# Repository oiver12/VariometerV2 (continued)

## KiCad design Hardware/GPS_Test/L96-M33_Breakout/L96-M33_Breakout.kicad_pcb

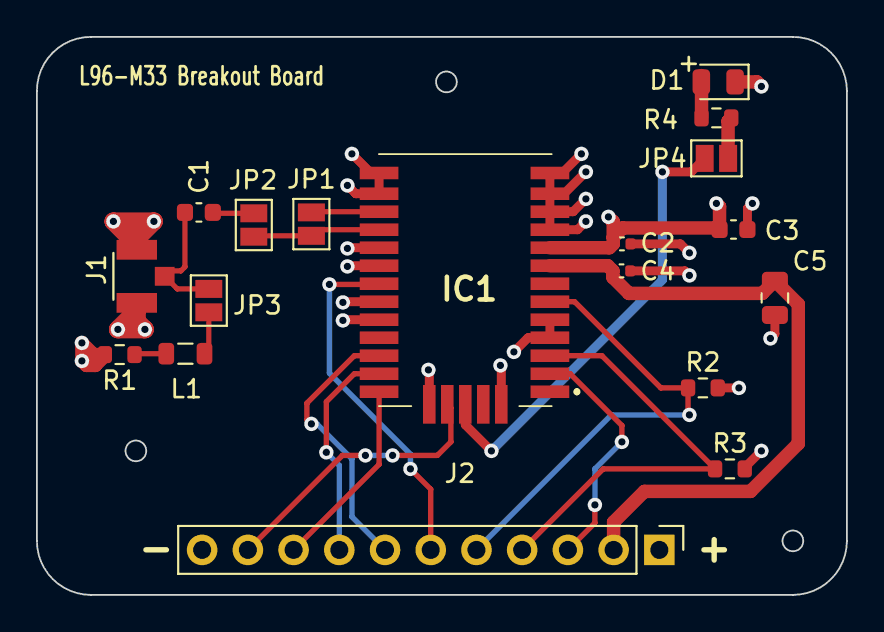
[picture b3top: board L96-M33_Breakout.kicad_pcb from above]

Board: 4 copper layers, 45.0 x 31.0 mm, 18 parts (0 on the bottom side), 20 nets.

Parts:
C1: 100pF; C_0603_1608Metric
C2, C4: 100nF; C_0402_1005Metric
C3: 10uF; C_0603_1608Metric
C5: 4.7uF; C_0805_2012Metric
D1: BLUE; LED_0805_2012Metric
IC1: L96-M33; L96
J1: U.FL-R-SMT(01); HRS_U.FL-R-SMT(01)
J2: Conn_01x11; PinHeader_1x11_P2.54mm_Vertical
JP1, JP2, JP3: SJ; SolderJumper-2_P1.3mm_Open_Pad1.0x1.5mm
JP4: JMP; SolderJumper-2_P1.3mm_Open_Pad1.0x1.5mm
L1: 47nH; L_0805_2012Metric
R1: 10R; R_0603_1608Metric
R2, R3: 4.7k; R_0603_1608Metric
R4: 1k; R_0603_1608Metric

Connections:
3D_FIX: IC1.2 (3D_FIX), J2.3
+3.3V: C2.2, C3.2, IC1.9 (VDD), J2.1, R1.2, R2.2, R3.2
+BATT: C4.2, C5.2, IC1.8 (V_BCKP), J2.2
FORCE_ON: IC1.28 (FORCE_ON), J2.10
GEO_FENCE: IC1.24 (GEO_FENCE), J2.7
GND: C2.1, C3.1, C4.1, C5.1, D1.1 (K), IC1.4 (GND1), IC1.5 (GND2), IC1.10 (GND3), IC1.11 (GND4), IC1.12 (GND5), IC1.13 (GND6), IC1.14 (GND7), IC1.15 (GND8), IC1.18 (GND9), IC1.19 (GND10), IC1.21 (GND11), IC1.22 (GND12), IC1.27 (GND13), IC1.31 (GND14), J1.1 (GND), J1.2 (GND), J2.11
JAM_DET: IC1.20 (JAM_DET), J2.6
unnamed: D1.2 (A), R4.2
unnamed: C1.1, J1.3 (SIG), JP3.1 (A)
unnamed: C1.2, JP2.2 (B)
unnamed: JP3.2 (B), L1.1
unnamed: JP4.1 (A), R4.1
unnamed: L1.2, R1.1
PPS: IC1.29 (TIMEPULSE), JP4.2 (B)
RF_IN: IC1.17 (RF_IN), JP1.2 (B), JP2.1 (A)
RF_OUT: IC1.16 (RF_OUT), JP1.1 (A)
RX: IC1.26 (RXD1), J2.9
SCL: IC1.6 (I2C_SCL), J2.5, R2.1
SDA: IC1.3 (I2C_SDA), J2.4, R3.1
TX: IC1.25 (TXD1), J2.8

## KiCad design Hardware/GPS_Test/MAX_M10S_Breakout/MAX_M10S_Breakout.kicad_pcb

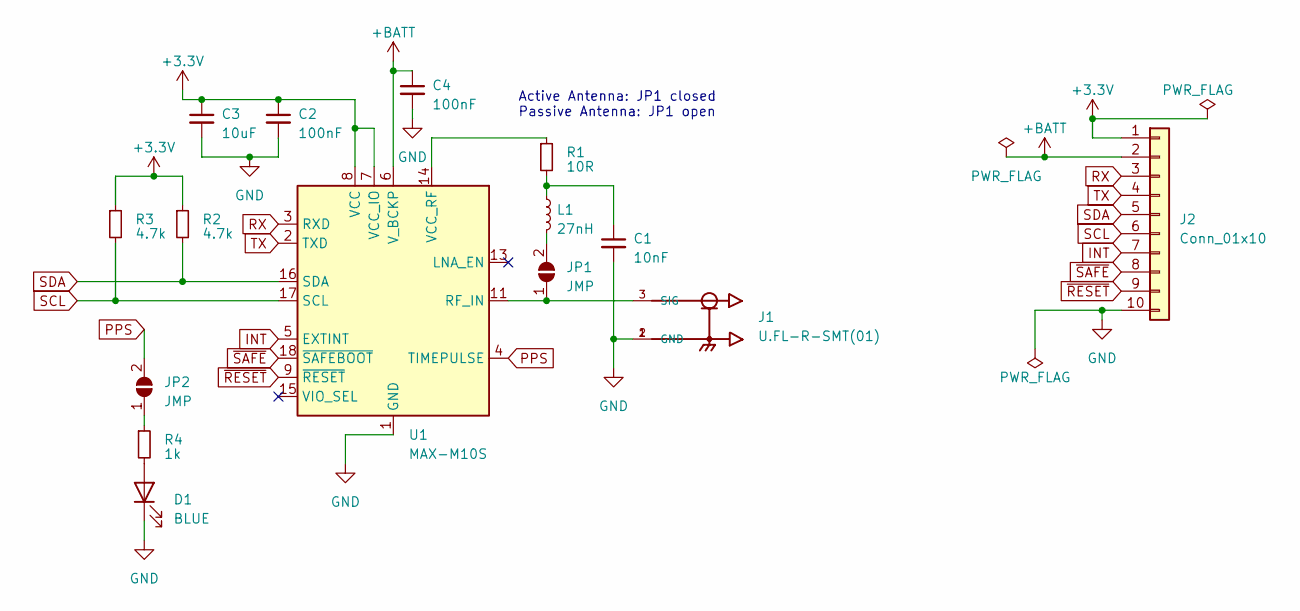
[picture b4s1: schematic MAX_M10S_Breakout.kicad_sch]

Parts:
C1: 10nF; C_0603_1608Metric; LCSC Part C57112
C2, C4: 100nF; C_0402_1005Metric; LCSC Part C307331
C3: 10uF; C_0603_1608Metric; LCSC Part C19702
D1: BLUE; LED_0603_1608Metric; LCSC Part C72041
J1: U.FL-R-SMT(01); HRS_U.FL-R-SMT(01)
J2: Conn_01x10; PinHeader_1x10_P2.54mm_Vertical
JP1, JP2: JMP; SolderJumper-2_P1.3mm_Open_Pad1.0x1.5mm
L1: 27nH; L_0603_1608Metric; LCSC Part C148128
R1: 10R; R_0402_1005Metric; LCSC Part C25077
R2, R3: 4.7k; R_0402_1005Metric; LCSC Part C25900
R4: 1k; R_0603_1608Metric; LCSC Part C21190
U1: MAX-M10S; ublox_MAX

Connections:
+3.3V: C2.1, C3.1, J2.1, R2.1, R3.1, U1.7 (VCC_IO), U1.8 (VCC)
+BATT: C4.1, J2.2, U1.6 (V_BCKP); also elsewhere on the board
GND: C1.2, C2.2, C3.2, C4.2, D1.1 (K), J1.1 (GND), J1.2 (GND), J2.10, U1.1 (GND), U1.10 (GND), U1.12 (GND); also elsewhere on the board
INT: J2.7, U1.5 (EXTINT)
unnamed: C1.1, L1.1, R1.2
unnamed: D1.2 (A), R4.2
unnamed: J1.3 (SIG), JP1.1 (A), U1.11 (RF_IN)
unnamed: JP1.2 (B), L1.2
unnamed: JP2.1 (A), R4.1
unnamed: R1.1, U1.14 (VCC_RF)
PPS: JP2.2 (B), U1.4 (TIMEPULSE)
RX: J2.3, U1.3 (RXD)
SCL: J2.6, R3.2, U1.17 (SCL)
SDA: J2.5, R2.2, U1.16 (SDA)
TX: J2.4, U1.2 (TXD)
~RESET: J2.9, U1.9 (~RESET)
~SAFE: J2.8, U1.18 (~SAFEBOOT)

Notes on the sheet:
Active Antenna: JP1 closed Passive Antenna: JP1 open

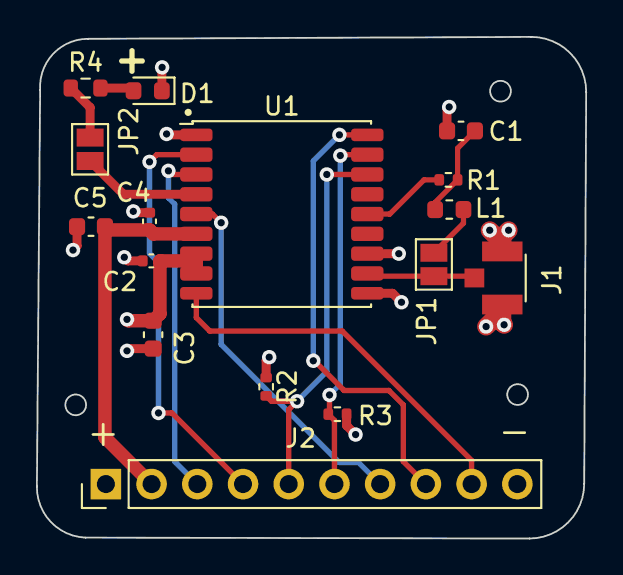
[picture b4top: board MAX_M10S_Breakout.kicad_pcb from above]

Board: 4 copper layers, 30.5 x 27.9 mm, 16 parts (0 on the bottom side), 17 nets.

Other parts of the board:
C5: 4.7uF; C_0603_1608Metric

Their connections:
+BATT: C5.1; also elsewhere on the board
GND: C5.2; also elsewhere on the board

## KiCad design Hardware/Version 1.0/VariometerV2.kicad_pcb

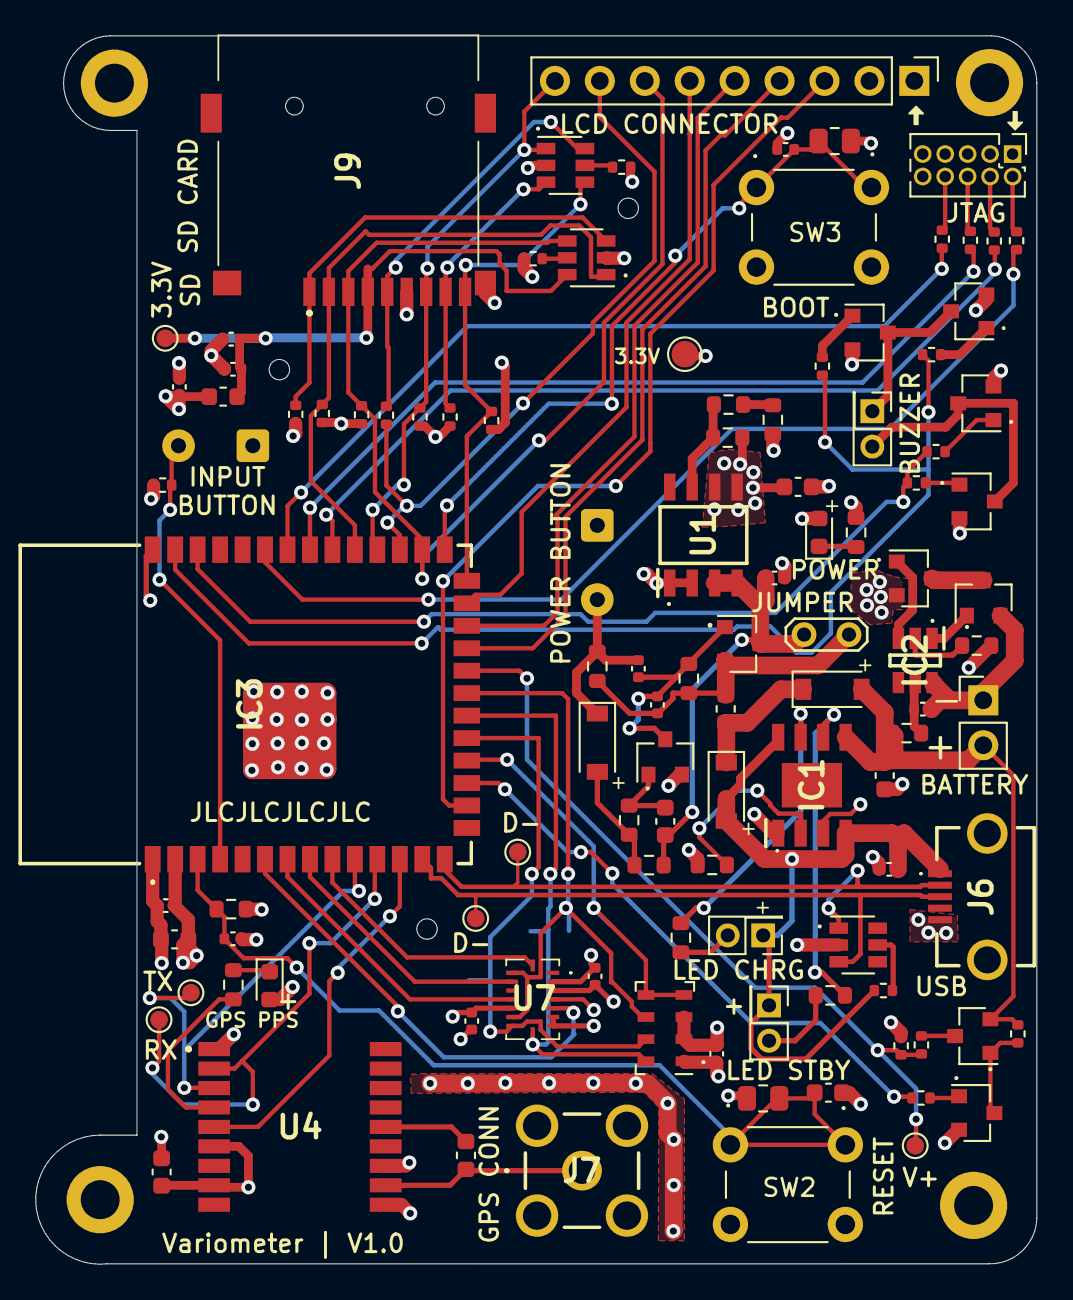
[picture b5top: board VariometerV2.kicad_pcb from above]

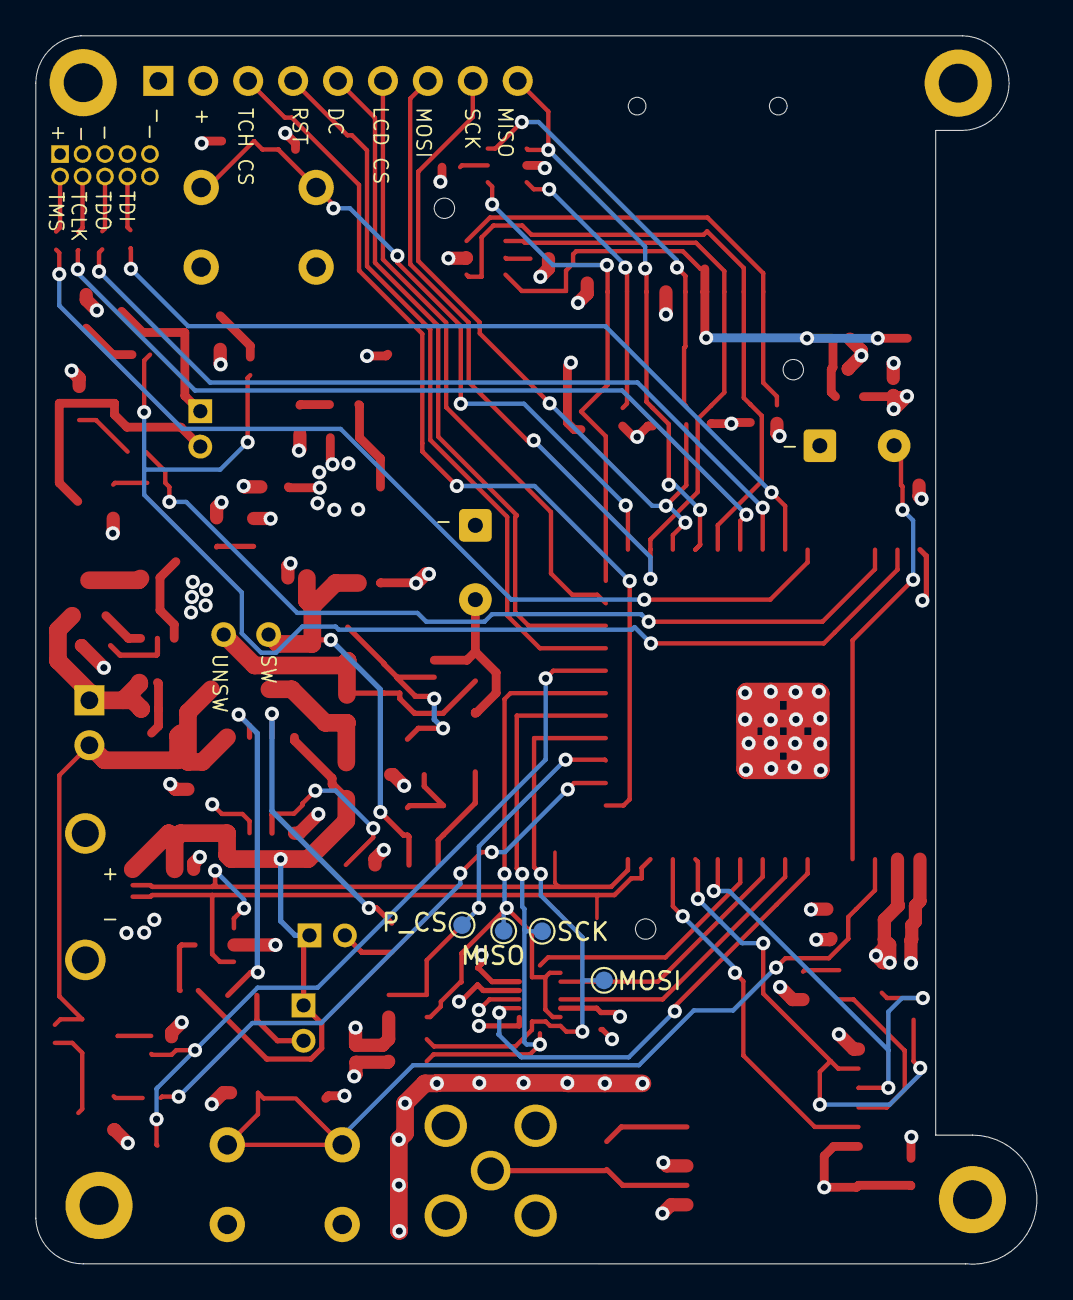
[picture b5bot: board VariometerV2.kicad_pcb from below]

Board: 4 copper layers, 56.6 x 69.4 mm, 117 parts (4 on the bottom side), 82 nets.

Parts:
C1, C2, C5, C7, C10, C13, C18, C19, C20, C21: 100nF; C_0402_1005Metric
C3, C6, C8, C9, C12, C15: 10uF; C_0603_1608Metric
C4, C11: 1uF; C_0402_1005Metric
C16, C17: 2.2uF; C_0402_1005Metric
D1, D2, D3: B5819W SL; D_SOD-123
D4: RED; LED_0603_1608Metric
D5: BLUE; LED_0603_1608Metric
F1: 1A; Fuse_0603_1608Metric
FB1: 600 @ 100 MHz; L_0603_1608Metric
H1, H2, H3, H4: MountingHole_Pad; MountingHole_2.2mm_M2_DIN965_Pad
IC1: TP4056; SOIC127P600X175-9N
IC2: DW01A-G; SOT95P280X135-6N
IC3: ESP32-S3-WROOM-1; ESP32S3WROOM1
J1: LED_CHRG; PinHeader_2x01_P2.00mm_Vertical
J2: LED_STBY; PinHeader_2x01_P2.00mm_Vertical
J3: TFT_LCD_CONNECTOR; PinHeader_1x09_P2.54mm_Vertical
J4: Conn_01x02_Male; PinHeader_1x02_P2.54mm_Vertical
J5: SWD; PinHeader_2x05_P1.27mm_Vertical
J6: USB3135-30-A; USB313530A
J7: 5-1814832-2; 518148322
J8: Conn_02x01; PinHeader_2x01_P2.00mm_Vertical
J9: TFP09-2-12B; TFP09212B
JP1: Jumper_2_Open; TestPoint_2Pads_Pitch2.54mm_Drill0.8mm
L1: 47nH; L_0603_1608Metric
Q1, Q2, Q4, Q6, Q8, Q10: AO3400A; SOT-23
Q3, Q5, Q7, Q9: AO3401A; SOT-23
R1: 1.2k; R_0603_1608Metric
R2, R4, R5, R25: 1k; R_0603_1608Metric
R3: 100; R_0603_1608Metric
R6, R18: 10k; R_0603_1608Metric
R7, R9: 100k; R_0603_1608Metric
R8: 300k; R_0603_1608Metric
R10: 51k; R_0603_1608Metric
R11: 27k; R_0603_1608Metric
R12, R17: 1.5k; R_0603_1608Metric
R13, R38: 1M; R_0402_1005Metric
R14, R16, R24, R26, R27, R28, R29, R30, R31, R32, R33, R34, R36, R37: 10k; R_0402_1005Metric
R15: 33k; R_0402_1005Metric
R19: 4.7k; R_0402_1005Metric
R20, R21, R22, R23, R35: 22; R_0402_1005Metric
R39, R40: 0k; R_0805_2012Metric
SW1, SW4: SW_Push; SolderWire-0.25sqmm_1x02_P4.2mm_D0.65mm_OD1.7mm
SW2, SW3: Switch_SW_Push; SW_PUSH_6mm
TP1: 3.3V TP; TestPoint_Pad_D1.5mm
TP2: TP_3.3V_SD-Card; TestPoint_Pad_D1.0mm
TP3: TP_USB_D+; TestPoint_Pad_D1.0mm
TP4: TP_USB_D-; TestPoint_Pad_D1.0mm
TP5: TP_BATTERY; TestPoint_Pad_D1.0mm
TP6: TP_TX; TestPoint_Pad_D1.0mm
TP7: TP_RX; TestPoint_Pad_D1.0mm
TP8: TP_SPI1_SCK; TestPoint_Pad_D1.0mm
TP9: TP_SPI1_MOSI; TestPoint_Pad_D1.0mm
TP10: TP_SPI1_MISO; TestPoint_Pad_D1.0mm
TP11: TP_PresSens_CS; TestPoint_Pad_D1.0mm
U1: TPS76801QDR; SOIC127P600X175-8N
U2, U5, U6: SRV05-4; SOT-23-6
U4: ATGM336H-5N31; ATGM336H5N31
U7: BMI088
U8: MS5611-01BA; LGA-8_3x5mm_P1.25mm

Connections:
3.3V_SDCARD: C17.1, C18.1, FB1.2, J9.4 (VDD), TP2.1, U5.6 (IO4)
+3V3: C8.1, C9.1, C10.1, C15.1, C16.1, C19.1, C20.1, C21.1, D4.2 (A), D5.2 (A), FB1.1, IC3.2 (3V3), J3.2, J5.1, Q7.2 (S), Q9.2 (S), R10.1, R18.1, R19.1, R30.1, R31.1, R32.1, R33.1, R34.1, R36.1, R37.2, R39.1, R40.1, TP1.1, U1.5 (OUT), U1.6 (OUT), U4.6 (VBAT), U4.8 (VCC), U7.3 (VDD), U7.11 (VDDIO), U8.1 (VDD)
+5V: C1.1, D2.2 (A), IC1.4 (VCC), IC1.8 (CE), J1.1, J2.1, J6.1, R24.1
ACC_INT: IC3.9 (IO16), U7.16 (INT1)
BATT+: C3.1, D1.2 (A), IC1.5 (BAT), J4.2, Q5.2 (S), R3.2, R13.2
BATT_CONN-: C2.1, IC2.6 (GND), J4.1, Q2.2 (S)
BAT_ADC: IC3.22 (IO14), R14.1, R15.2, TP5.1
BAT_MS: IC3.17 (IO9), R16.1
Button_Input: IC3.4 (IO4), R19.2, SW4.2
DW01A_OC: IC2.3 (OC), Q1.1 (G)
DW01A_OD: IC2.1 (OD), Q2.1 (G)
EN: C11.1, C12.1, IC3.3 (EN), R18.2, R39.2, SW2.1
GND: C1.2, C3.2, C7.2, C8.2, C9.2, C10.2, C11.2, C12.2, C13.2, C15.2, C16.2, C17.2, C18.2, C19.2, C20.2, C21.2, H1.1, H2.1, H3.1, H4.1, IC1.1 (Temp), IC1.3 (GND), IC3.1 (GND_1), IC3.40 (GND_2), IC3.41 (GND_3), IC3.42 (GND_4), IC3.43 (GND_5), IC3.44 (GND_6), IC3.45 (GND_7), IC3.46 (GND_8), IC3.47 (GND_9), IC3.48 (GND_10), IC3.49 (GND_11), J3.1, J5.3, J5.5, J5.9, J6.5, J6.MH1, J6.MH2, J7.2, J7.3 (2), J7.4 (2), J7.5 (2), J9.6 (VSS), J9.10 (GND), Q1.2 (S), Q4.2 (S), Q6.2 (S), Q8.2 (S), Q10.2 (S), R1.1, R2.2, R12.2, R15.1, R17.2, R38.2, SW1.1, SW2.2, SW3.2, SW4.1, U1.1 (GND), U1.2 (EN#), U2.2 (VN), U4.1 (GND), U4.10 (GND), U4.12 (GND), U5.2 (VN), U6.2 (VN), U7.2 (NC), U7.4 (GNDA), U7.6 (GNDIO), U7.7 (PS), U8.2 (PS), U8.3 (GND)
GPS_ON: IC3.12 (IO8), U4.5 (ON/OFF)
GPS_PPS: R25.2, U4.4 (1PPS)
GYR_INT: IC3.7 (IO7), U7.12 (INT3)
IMU_ACC_CS: IC3.8 (IO15), U7.14 (CSB1)
IMU_GYR_CS: IC3.6 (IO6), U7.5 (CSB2)
IO0: C13.1, IC3.27 (IO0), R40.2, SW3.1
JTAG_TCLK: IC3.32 (IO39), R21.2
JTAG_TDI: IC3.34 (IO41), R23.2
JTAG_TDO: IC3.33 (IO40), R22.2
JTAG_TMS: IC3.35 (IO42), R20.2
LCD_CS: IC3.25 (IO48), J3.6
LCD_DC: IC3.24 (IO47), J3.5
LCD_RST: IC3.23 (IO21), J3.4
LCD_TCH_CS: IC3.16 (IO46), J3.3
unnamed: C2.2, IC2.5 (VCC), R3.1
unnamed: C4.1, C5.1, Q3.1 (G), Q4.3 (D), R7.2
unnamed: C4.2, D3.1 (K), R6.2, SW1.2
unnamed: C6.1, Q4.1 (G), R8.2
unnamed: D1.1 (K), D2.1 (K), F1.2
unnamed: D3.2 (A), R8.1, R9.2
unnamed: D4.1 (K), R17.1
unnamed: D5.1 (K), R25.1
unnamed: IC1.2 (PROG), R1.2
unnamed: IC2.2 (CS), R2.1
unnamed: J1.2, R4.1
unnamed: J2.2, R5.1
unnamed: J5.2, R20.1
unnamed: J5.4, R21.1
unnamed: J5.6, R22.1
unnamed: J5.8, R23.1
unnamed: J7.1, L1.1, U4.11 (RF_IN)
unnamed: J8.1, Q7.3 (D), Q8.3 (D)
unnamed: J8.2, Q9.3 (D), Q10.3 (D)
unnamed: J9.1 (DAT2), R30.2, U5.3 (IO2)
unnamed: J9.5 (CLK), R35.2, U6.6 (IO4)
unnamed: J9.8 (DAT1), R34.2, U6.3 (IO2)
unnamed: L1.2, U4.14 (VCC_RF)
unnamed: Q1.3 (D), Q2.3 (D)
unnamed: Q5.1 (G), Q6.3 (D), R13.1
unnamed: Q5.3 (D), R14.2
unnamed: Q6.1 (G), R16.2
unnamed: Q7.1 (G), R26.1
unnamed: Q8.1 (G), R27.1
unnamed: Q9.1 (G), R28.2
unnamed: Q10.1 (G), R29.2
unnamed: R10.2, R11.1, U1.7 (FB/NC)
unnamed: R11.2, R12.1
unnamed: R24.2, U2.5 (VP)
unnamed: R36.2, U5.5 (VP)
unnamed: R37.1, U6.5 (VP)
POW_SW+: C6.2, C7.1, JP1.2 (B), Q3.3 (D), R9.1, U1.3 (IN), U1.4 (IN)
POW_UNSW+: C5.2, F1.1, JP1.1 (A), Q3.2 (S), R6.1, R7.1
PresSens_CS: IC3.18 (IO10), TP11.1, U8.4 (CSB), U8.5 (CSB)
SDCARD_CS: IC3.31 (IO38), J9.2 (CD/DAT3), R31.2, U5.1 (IO1)
SDCARD_DETECT: IC3.26 (IO45), J9.9 (CARD_DETECTION), R38.1, U6.4 (IO3)
SPI1_MISO: IC3.21 (IO13), TP10.1, U7.10 (SDO2), U7.15 (SDO1), U8.6 (SDO)
SPI1_MOSI: IC3.19 (IO11), TP9.1, U7.9 (SDI), U8.7 (SDI/SDA)
SPI1_SCK: IC3.20 (IO12), TP8.1, U7.8 (SCK), U8.8 (SCLK)
SPI2_MISO: IC3.30 (IO37), J3.9, J9.7 (DAT0), R33.2, U6.1 (IO1)
SPI2_MOSI: IC3.28 (IO35), J3.7, J9.3 (CMD), R32.2, U5.4 (IO3)
SPI2_SCK: IC3.29 (IO36), J3.8, R35.1
TIM1_CH1: IC3.39 (IO1), R26.2, R27.2
TIM1_CH1N: IC3.38 (IO2), R28.1, R29.1
TP4056_CHRG: IC1.7 (CHRG), R4.2
TP4056_STBY: IC1.6 (STDBY), R5.2
USART2_RX: IC3.11 (IO18), TP7.1, U4.2 (TXD)
USART2_TX: IC3.10 (IO17), TP6.1, U4.3 (RXD)
USB_D+: IC3.14 (IO20), J6.2, TP3.1, U2.1 (IO1)
USB_D-: IC3.13 (IO19), J6.3, TP4.1, U2.3 (IO2)

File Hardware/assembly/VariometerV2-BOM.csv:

Comment,Designator,Footprint,LCSC
"100nF","C1,C2,C5,C7,C10,C13,C18,C19,C20,C21","Capacitor_SMD:C_0402_1005Metric","C307331"
"2.2uF","C16,C17","Capacitor_SMD:C_0402_1005Metric","C12530"
"10uF","C3,C6,C8,C9,C12,C15","Capacitor_SMD:C_0603_1608Metric","C19702"
"1uF","C4,C11","Capacitor_SMD:C_0402_1005Metric","C52923"
"B5819W SL","D1,D2,D3","Diode_SMD:D_SOD-123","C8598"
"RED","D4","LED_SMD:LED_0603_1608Metric","C2286"
"BLUE","D5","LED_SMD:LED_0603_1608Metric","C72041"
"1A","F1","Fuse:Fuse_0603_1608Metric","C516069"
"600 @ 100 MHz","FB1","Inductor_SMD:L_0603_1608Metric","C1002"
"MountingHole_Pad","H1,H2,H3,H4","MountingHole:MountingHole_2.2mm_M2_DIN965_Pad",""
"TP4056","IC1","Hardware:SOIC127P600X175-9N","C16581"
"DW01A-G","IC2","Hardware:SOT95P280X135-6N","C61503"
"ESP32-S3-WROOM-1","IC3","Hardware:ESP32S3WROOM1","C2913198"
"LED_CHRG","J1","Connector_PinHeader_2.00mm:PinHeader_2x01_P2.00mm_Vertical",""
"LED_STBY","J2","Connector_PinHeader_2.00mm:PinHeader_2x01_P2.00mm_Vertical",""
"TFT_LCD_CONNECTOR","J3","Connector_PinHeader_2.54mm:PinHeader_1x09_P2.54mm_Vertical",""
"Conn_01x02_Male","J4","Connector_PinHeader_2.54mm:PinHeader_1x02_P2.54mm_Vertical",""
"SWD","J5","Connector_PinHeader_1.27mm:PinHeader_2x05_P1.27mm_Vertical",""
"USB3135-30-A","J6","Hardware:USB313530A",""
"5-1814832-2","J7","Hardware:518148322",""
"Conn_02x01","J8","Connector_PinHeader_2.00mm:PinHeader_2x01_P2.00mm_Vertical",""
"TFP09-2-12B","J9","Hardware:TFP09212B",""
"Jumper_2_Open","JP1","TestPoint:TestPoint_2Pads_Pitch2.54mm_Drill0.8mm",""
"47nH","L1","Inductor_SMD:L_0603_1608Metric","C346317"
"AO3400A","Q1,Q2,Q4,Q6,Q8,Q10","Package_TO_SOT_SMD:SOT-23","C20917"
"AO3401A","Q3,Q5,Q7,Q9","Package_TO_SOT_SMD:SOT-23","C15127"
"1.2k","R1","Resistor_SMD:R_0603_1608Metric","C22765"
"51k","R10","Resistor_SMD:R_0603_1608Metric","C23196"
"27k","R11","Resistor_SMD:R_0603_1608Metric","C22967"
"1.5k","R12,R17","Resistor_SMD:R_0603_1608Metric","C22843"
"1M","R13,R38","Resistor_SMD:R_0402_1005Metric","C26083"
"10k","R14,R16,R24,R26,R27,R28,R29,R30,R31,R32,R33,R34,R36,R37","Resistor_SMD:R_0402_1005Metric","C25744"
"33k","R15","Resistor_SMD:R_0402_1005Metric","C25779"
"4.7k","R19","Resistor_SMD:R_0402_1005Metric","C25900"
"1k","R2,R4,R5,R25","Resistor_SMD:R_0603_1608Metric","C21190"
"22","R20,R21,R22,R23,R35","Resistor_SMD:R_0402_1005Metric","C25092"
"100","R3","Resistor_SMD:R_0603_1608Metric","C22775"
"0k","R39,R40","Resistor_SMD:R_0805_2012Metric",""
"10k","R6,R18","Resistor_SMD:R_0603_1608Metric","C25804"
"100k","R7,R9","Resistor_SMD:R_0603_1608Metric","C25803"
"300k","R8","Resistor_SMD:R_0603_1608Metric","C23024"
"SW_Push","SW1,SW4","Connector_Wire:SolderWire-0.25sqmm_1x02_P4.2mm_D0.65mm_OD1.7mm",""
"Switch_SW_Push","SW2,SW3","Button_Switch_THT:SW_PUSH_6mm",""
"3.3V TP","TP1","TestPoint:TestPoint_Pad_D1.5mm",""
"TP_SPI1_MISO","TP10","TestPoint:TestPoint_Pad_D1.0mm",""
"TP_PresSens_CS","TP11","TestPoint:TestPoint_Pad_D1.0mm",""
"TP_3.3V_SD-Card","TP2","TestPoint:TestPoint_Pad_D1.0mm",""
"TP_USB_D+","TP3","TestPoint:TestPoint_Pad_D1.0mm",""
"TP_USB_D-","TP4","TestPoint:TestPoint_Pad_D1.0mm",""
"TP_BATTERY","TP5","TestPoint:TestPoint_Pad_D1.0mm",""
"TP_TX","TP6","TestPoint:TestPoint_Pad_D1.0mm",""
"TP_RX","TP7","TestPoint:TestPoint_Pad_D1.0mm",""
"TP_SPI1_SCK","TP8","TestPoint:TestPoint_Pad_D1.0mm",""
"TP_SPI1_MOSI","TP9","TestPoint:TestPoint_Pad_D1.0mm",""
"TPS76801QDR","U1","Hardware:SOIC127P600X175-8N","C20030"
"SRV05-4","U2,U5,U6","Package_TO_SOT_SMD:SOT-23-6","C85364"
"ATGM336H-5N31","U4","Hardware:ATGM336H5N31","C90770"
"BMI088","U7","Hardware:BMI088","C194919"
"MS5611-01BA","U8","Package_LGA:LGA-8_3x5mm_P1.25mm","C37148"

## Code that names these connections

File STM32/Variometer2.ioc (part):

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Mcu.Name=STM32F745V(E-G)Tx
Mcu.Package=LQFP100
Mcu.UserName=STM32F745VETx
PA1.GPIOParameters=GPIO_Label
PA1.GPIO_Label=GPS_PPS
PA1.Signal=GPIO_Input
PA10.Mode=Asynchronous
PA10.Signal=USART1_RX
PA11.Mode=Device_Only
PA11.Signal=USB_OTG_FS_DM
PA12.Mode=Device_Only
PA12.Signal=USB_OTG_FS_DP
PA13.Mode=Trace_Asynchronous_SW
PA13.Signal=SYS_JTMS-SWDIO
PA14.Mode=Trace_Asynchronous_SW
PA14.Signal=SYS_JTCK-SWCLK
PA2.Mode=Asynchronous
PA2.Signal=USART2_TX
PA3.Mode=Asynchronous
PA3.Signal=USART2_RX
PA4.GPIOParameters=GPIO_Label
PA4.GPIO_Label=GPS_ON/OFF
PA4.Signal=GPIO_Output
PA5.Mode=Full_Duplex_Master
PA5.Signal=SPI1_SCK
PA6.Mode=Full_Duplex_Master
PA6.Signal=SPI1_MISO
PA7.Mode=Full_Duplex_Master
PA7.Signal=SPI1_MOSI
PA9.Mode=Asynchronous
PA9.Signal=USART1_TX
PB0.GPIOParameters=GPIO_Label
PB0.GPIO_Label=IMU_GYR_CS
PB0.Signal=GPIO_Output
PB1.GPIOParameters=GPIO_Label
PB1.GPIO_Label=ACC_INT
PB1.Signal=GPXTI1
PB13.GPIOParameters=GPIO_Label
PB13.GPIO_Label=BLE_LED
PB13.Signal=GPIO_Output
PB14.GPIOParameters=GPIO_Label
PB14.GPIO_Label=GPS_LED
PB14.Signal=GPIO_Output
PB15.GPIOParameters=GPIO_Label
PB15.GPIO_Label=ERROR_LED
PB15.Signal=GPIO_Output
PB2.GPIOParameters=GPIO_Label
PB2.GPIO_Label=GYR_INT
PB2.Signal=GPXTI2
PB3.Mode=Trace_Asynchronous_SW
PB3.Signal=SYS_JTDO-SWO
PC0.GPIOParameters=GPIO_Label
PC0.GPIO_Label=BAT_ADC
PC0.Signal=ADCx_IN10
PC10.Mode=SD_4_bits_Wide_bus
PC10.Signal=SDMMC1_D2
PC11.Mode=SD_4_bits_Wide_bus
PC11.Signal=SDMMC1_D3
PC12.Mode=SD_4_bits_Wide_bus
PC12.Signal=SDMMC1_CK
PC14/OSC32_IN.GPIOParameters=GPIO_Label
PC14/OSC32_IN.GPIO_Label=BAT_MS
PC14/OSC32_IN.Signal=GPIO_Output
PC5.GPIOParameters=GPIO_Label
PC5.GPIO_Label=IMU_ACC_CS
PC5.Signal=GPIO_Output
PC6.GPIOParameters=GPIO_Label
PC6.GPIO_Label=BLE_DATA
PC6.Signal=GPIO_Input
PC7.GPIOParameters=GPIO_Label
PC7.GPIO_Label=BLE_nRESET
PC7.Signal=GPIO_Output
PC8.Mode=SD_4_bits_Wide_bus
PC8.Signal=SDMMC1_D0
PC9.Mode=SD_4_bits_Wide_bus
PC9.Signal=SDMMC1_D1
PD11.GPIOParameters=GPIO_Label
PD11.GPIO_Label=BLE_LINK
PD11.Signal=GPIO_Input
PD12.Mode=I2C
PD12.Signal=I2C4_SCL
PD13.Mode=I2C
PD13.Signal=I2C4_SDA
PD14.GPIOParameters=GPIO_Label
PD14.GPIO_Label=BLE_SLEEP
PD14.Signal=GPIO_Output
PD15.GPIOParameters=GPIO_Label
PD15.GPIO_Label=BLE_MODE
PD15.Signal=GPIO_Output
PD2.Mode=SD_4_bits_Wide_bus
PD2.Signal=SDMMC1_CMD
PD4.GPIOParameters=GPIO_Label
PD4.GPIO_Label=SDCARD_DETECT
PD4.Signal=GPIO_Input
PE0.GPIOParameters=GPIO_PuPd,GPIO_Label
PE0.GPIO_Label=Button_Input
PE0.GPIO_PuPd=GPIO_PULLDOWN
PE0.Signal=GPIO_Input
PE15.GPIOParameters=GPIO_Label
PE15.GPIO_Label=PresSen_CS
PE15.Signal=GPIO_Output
PE8.Mode=Output Compare1 CH1 CH1N
PE8.Signal=TIM1_CH1N
PE9.Signal=S_TIM1_CH1
PH0/OSC_IN.Mode=HSE-External-Oscillator
PH0/OSC_IN.Signal=RCC_OSC_IN
PH1/OSC_OUT.Mode=HSE-External-Oscillator
PH1/OSC_OUT.Signal=RCC_OSC_OUT
RCC.HSE_VALUE=16000000
board=custom

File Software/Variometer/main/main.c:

#include <stdio.h>
#include <esp_log.h>
#include <driver/gpio.h>
#include "nmea_parser.h"
#include "SDCard.h"
#include "main.h"
#include "BatteryManager.h"
#include "SoundManager.h"
#include "IGC/IGCLogger.h"
#include "TestTools/FlightLogger.h"
#include "DeviceContext.h"
#include "Screen/Display_Vario.h"
#include "ButtonInput.h"
#include "AGL.h"
#include "Flash/flashMemory.h"
#include "AirspaceParcer/airspaceParcer.h"
#include "MainTasks.h"
#include "Bluetooth/bluetooth.h"
#include "ErrorHandling.h"

#define POWSW_ENABLE 13

#define I2C_MASTER_FREQ_HZ 80000
#define I2C_SDA 37
#define I2C_SCL 36
#define i2c_master_port 0

#define USART2_TX 17
#define USART2_RX 18

/* GPS */
#define TIME_ZONE (+1)   // Schweiz
#define YEAR_BASE (2000) // date in GPS starts from 2000

static const char *TAG = "main";

// void sendAttitude(void *params)
// {
//     float rotation[4];
//     // float roll = 0.0f, pitch = 0.0f, yaw = 0.0f;
//     while (1)
//     {
//         // Quaternion_get_RPY(rotation[0], rotation[1], rotation[2], rotation[3], &roll, &pitch, &tmep);
//         // fwrite(&roll, sizeof(float), 1, stdout);
//         // fwrite(&pitch, sizeof(float), 1, stdout);
//         // fwrite(&yaw, sizeof(float), 1, stdout);
//         fwrite(&rotation, sizeof(float), 4, stdout);
//         char ending = 0xff;
//         fwrite(&ending, sizeof(char), 1, stdout);
//         printf("\n");
//         vTaskDelay(200 / portTICK_PERIOD_MS);
//     }
//     vTaskDelete(NULL);
// }

void app_main(void)
{
    esp_err_t err;
    gpio_config_t enableGPIOOutput = {
        .intr_type = GPIO_INTR_DISABLE,
        .mode = GPIO_MODE_OUTPUT,
        .pin_bit_mask = 1ULL << POWSW_ENABLE,
        .pull_down_en = 0,
        .pull_up_en = 0};

    err = gpio_config(&enableGPIOOutput);
    err |= gpio_set_level(POWSW_ENABLE, 1);
    if (err != ESP_OK)
    {
        error_handle(err, ERR_MAIN, "Can't initialize Power EN GPIO");
        return;
    }

    vTaskDelay(1000 / portTICK_PERIOD_MS);

    err = gpio_install_isr_service(ESP_INTR_FLAG_LEVEL1); // gpio interrupts are generally not that important
    if (err != ESP_OK)
    {
        error_handle(err, ERR_MAIN, "Can't initialize ISR Service");
    }

    // // /* Configure GPS Reader Library */
    nmea_parser_config_t gps_config = NMEA_PARSER_CONFIG_DEFAULT();
    gps_config.uart.rx_pin = USART2_RX;
    nmea_parser_handle_t gps_nmea_hdl = nmea_parser_init(&gps_config, 5 * 1024);
    ESP_LOGI(TAG, "GPS started");

    // sdcard_t *sdcard = calloc(sizeof(sdcard_t), 1);
    init_DeviceContext();

    err = init_sdcard("/sdcard");
    if (err == ESP_FAIL)
    {
        error_handle(err, ERR_SDCARD, "Can't mount File System");
    }
    else if (err != ESP_OK)
    {
        error_handle(err, ERR_SDCARD, "Can't initialite SD Card");
    }
    init_IGCLogger(gps_nmea_hdl);
    initLogging(gps_nmea_hdl);

    // gps handle wird beim DeviceContext erst nach SD Karte gestartet, da wenn direkt abfulg ist, soll
    // das loggen auf SDKarte direkt starten. Wenn die Sd Karte gestartet wird, muss jedoch device kontext
    // schon gestartet sein
    startGps_DeviceContext(gps_nmea_hdl);

    err = init_SoundManager();
    ERROR_HANDLEBYERROR(err, ERR_SOUNDMANAGER, "Can't start Sound Manager");

    err = init_Display();
    ERROR_HANDLEBYERROR(err, ERR_SCREEN, "Can't start display");

    err = flashMemoryInit();
    ERROR_HANDLEBYERROR(err, ERR_FLASH, "Can't start Flash");

    err = init_Battery_Manager(4);
    ERROR_HANDLEBYERROR(err, ERR_BATTERY, "Can't start Battery Manager");

    err = ButtonInput_Init();
    ERROR_HANDLEBYERROR(err, ERR_BUTTONS, "Can't start Button Manager");

    err = startLogging();
    ERROR_HANDLEBYERROR(err, ERR_LOGGING, "Can't start Testlogging");
    // AGL_startAGL(sdcard, gps_nmea_hdl);

    StartAirspaceParse();

    startBluetooth();

    vTaskDelay(100 / portTICK_PERIOD_MS);

    startMainTasks();
    // xTaskCreate(sendAttitude, "Send Attitude", 4 * 1024, NULL, 6, NULL);
    // perfmon_start();
    return;
}

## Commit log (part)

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2021-11-03 Add Hardware
2021-11-20 Fast fertig
2021-11-29 Fertig
2021-12-06 Schematic Finish
2021-12-31 PCB fast fertig
2022-01-03 PCB fertig
2022-01-13 gerber added
2022-01-14 readme
2022-01-18 esp32 start
2022-01-21 change
2022-01-28 create
2022-03-05 Variometer bestellt
2022-03-06 VSCode started
2022-03-11 Added Kalman Filter
2022-03-17 use I2C
2022-04-09 Change I2C
2022-07-29 Kalman Filter funktioniert
2022-08-27 V2.0 fertig
2022-09-05 Before Variometer V2.2
2022-09-10 Logging Functions
2022-09-20 ScreenTest_Start
2022-10-14 test
2022-10-16 screen
2022-10-17 flgithLogger
2022-11-11 case
2022-11-14 case follow
2022-11-21 case new
2022-12-14 EInk fast working
2022-12-15 E_Ink fast funktioniert
2022-12-16 Screen fast working
2022-12-25 Display fast working
2022-12-30 Bildschirm und Simulator
    -Bildschirm funktioniert
    -Vario Bildschirm Simulator erstellt
    -Bilder können als Buffer ausgegeben werden.
    -Paint Buffer können auf Bildschirm dargestellt werden
2022-12-30 Screen Simulator
2023-01-03 settings start implement
2023-01-14 v1.2 continue
2023-01-14 case_icons
2023-02-01 Buttons working / Case V. 1.3
2023-02-11 Settings fast
2023-02-25 start Airspace
2023-03-09 compass / attitude
2023-03-14 not everything works
2023-03-29 sdcard fix
2023-04-03 Test12
2023-04-05 Linux added
2023-04-10 Start GPS -Test-PCB
2023-04-10 MAX-M10S continue
2023-04-11 Weiter Max M10S
2023-04-11 Folder with cases from saemi. Many blender files, Oli will be pissed.
2023-04-13 Continue GPS Hardware
2023-04-14 Max-M10S finished
2023-04-14 added some boolean outlets
2023-04-17 case version 1.2.0 finished
2023-04-17 Change to esp-idf 5.1
2023-04-17 Fertig GPS Test Platine
2023-04-17 Threejs implementation start
2023-04-18 Rename Readme.me to Readme.md
2023-04-18 Rename Readme.md to README.md
2023-04-18 Fix Screen / Clenaup
2023-04-20 Start Board Devlopment
2023-04-21 Start Vario PCB
2023-04-24 Develop Board
2023-04-27 Working on PCB
2023-04-27 added spinning wheel
2023-04-27 spinning wheel modified
2023-04-27 dependency conflict fixed
2023-04-27 Weiter PCB
2023-04-28 Work on Linux Screen Simulator
2023-05-01 Info text and other smaller details added
2023-05-01 Update Schematics
2023-05-01 Screen Simulator with Height
2023-05-01 Product new pop up changed
2023-05-02 Work on PCB
2023-05-02 Update gitignores
2023-05-02 Change gitignore
2023-05-02 fucked up merge fixed
2023-05-02 pop up finished and info arrow started
2023-05-03 PCB/Screen_Simulator
2023-05-03 fuck me
2023-05-03 Add GPS Info Widget
2023-05-04 before dark theme remove
2023-05-04 second page added
2023-05-04 Add IGC Parser
2023-05-05 IGCParser
2023-05-06 Home page 'finished'
2023-05-07 IGC File Parser
2023-05-08 another try :(
2023-05-10 Add Flight End Screen
2023-05-11 Flight List
2023-05-12 Flig Stat
2023-05-14 three js integration2
2023-05-15 Changfe
2023-05-15 GPS Analyze
2023-05-17 Work on Airspace Parcer
2023-05-17 first and second page added at home for selling website
2023-05-19 sdaf
2023-05-19 Fix Vario Bugs
2023-05-19 New Changes
2023-05-21 GPS Test
2023-05-23 Airspaces
2023-05-23 Airspace Parcer
2023-05-23 AirspaceParcer
2023-05-23 Airspace parsing works on Variometer
2023-05-24 Optimize Airspace Parcer
2023-05-25 Airspace Fixes
2023-05-25 Fixes in Airspace
2023-05-26 GPS Test Files
2023-05-26 Caching IGC Parse
2023-05-30 Fix some Errors
2023-06-01 case version 2.9.0 finished
2023-06-01 Start on pcb
2023-06-02 svg added
2023-06-02 PCb Layout done
2023-06-02 Fix some Errors and Biep Mean
2023-06-05 PCb Work...
2023-06-05 WRL File
2023-06-06 Add Bluetooth BLE
2023-06-06 Bluetooth Works
2023-06-07 Routing ..
2023-06-08 PCB Routing Done
2023-06-08 New 3D File
2023-06-08 change buttons
2023-06-09 Finish PCB
2023-06-09 PCB Work
2023-06-12 FIX Main Tasks
2023-06-12 Fix Tasts Error
2023-06-13 Fix Screen Connector PCB
2023-06-14 Add proper Error Handling
2023-06-16 Start Track Point History
2023-06-19 Develop Thermik assistant
2023-06-21 I hate my fucking live
2023-06-24 FlightState
2023-06-29 Saemi changes
2023-06-29 Change to submodule
2023-06-30 Add Simulation
2023-06-30 Cleanup
2023-06-30 Start Simulation
2023-07-01 Simulation
2023-07-01 Change arrangement
2023-07-03 Refactor
2023-07-19 Simulation work
2023-10-15 simulation working
2024-04-25 New commit
2024-04-25 Working Simulator/IGc Parser
